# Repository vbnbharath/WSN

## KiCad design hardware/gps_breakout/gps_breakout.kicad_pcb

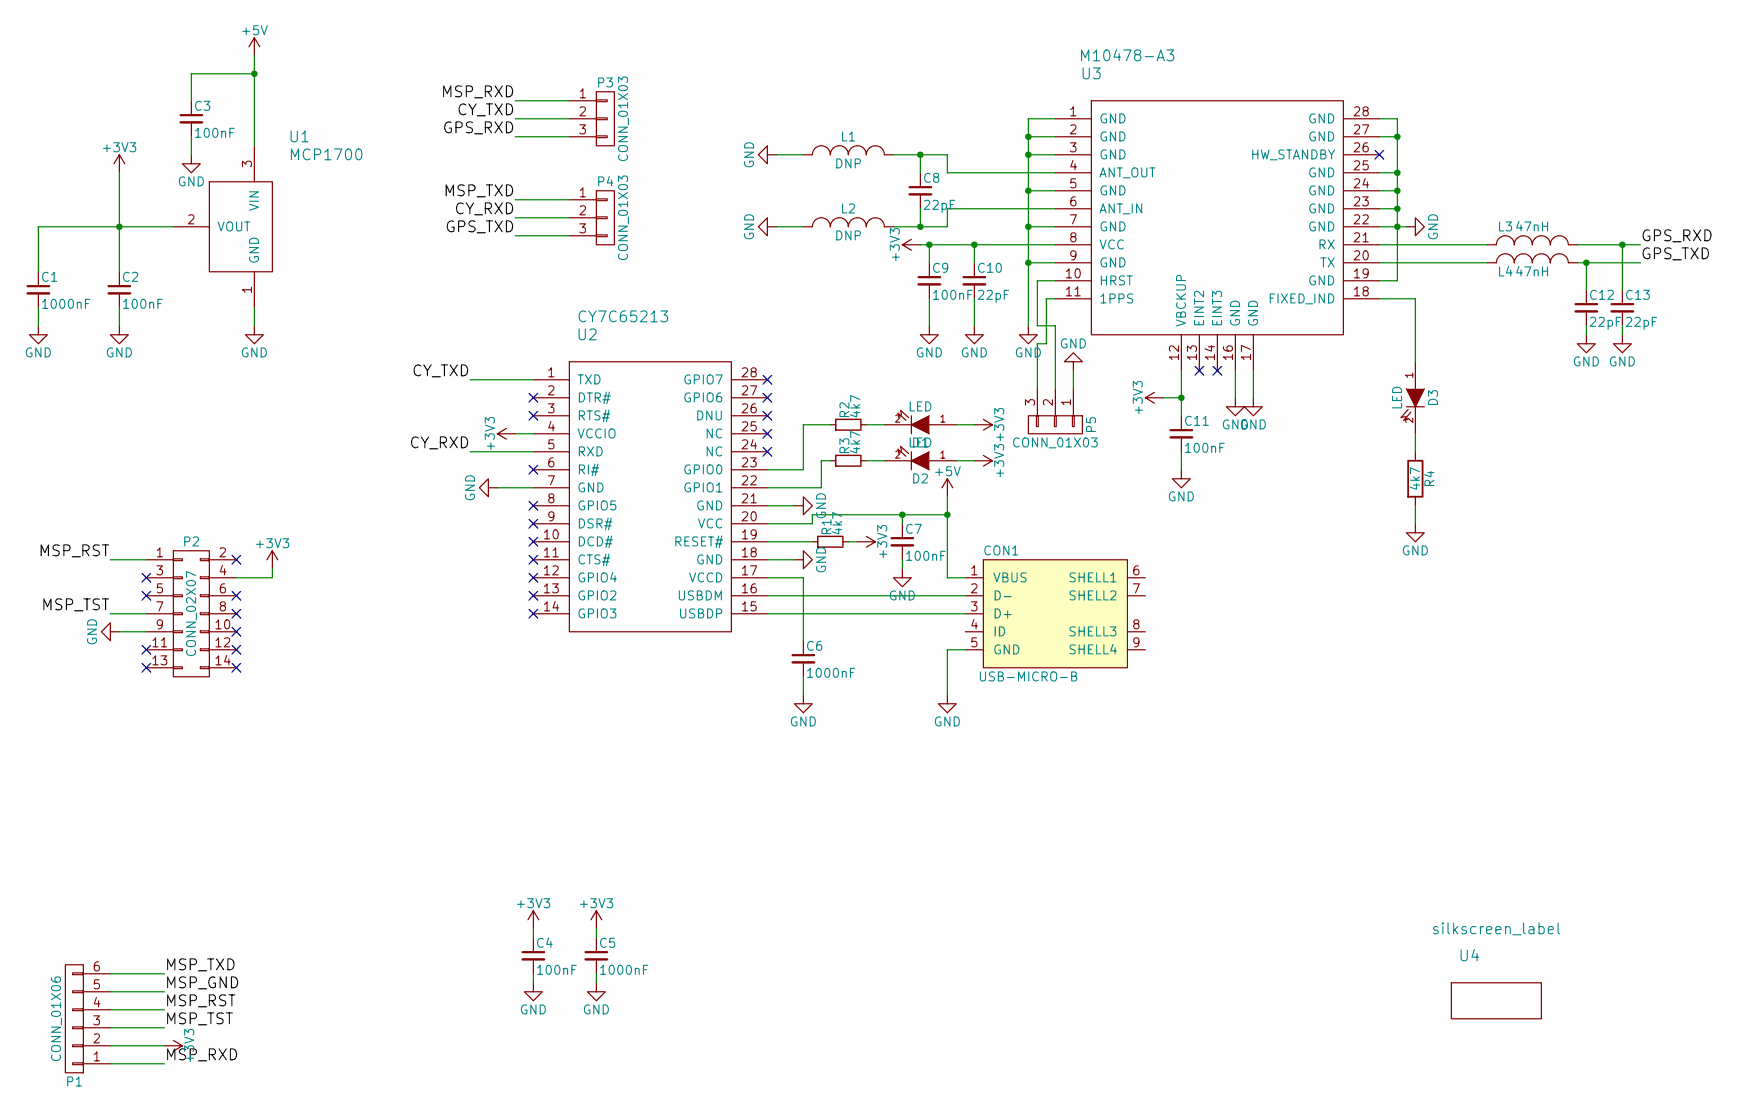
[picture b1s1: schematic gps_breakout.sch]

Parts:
C1, C5, C6: 1000nF; C_0603
C2, C3, C4, C7, C9, C11: 100nF; C_0603
C8, C10, C12, C13: 22pF; C_0603
CON1: USB-MICRO-B; USB_Mini-B
D1, D2, D3: LED; LED-0603
L1, L2: DNP; R_0603
L3, L4: 47nH; R_0603
P1: CONN_01X06; LPPB061NGCN-RC
P2: CONN_02X07; CONN_MSPJTAG
P3, P4, P5: CONN_01X03; JMP_HDR
R1, R2, R3, R4: 4k7; R_0603
U1: MCP1700; SOT89-3_Housing
U2: CY7C65213; SSOP-28_5.3x10.2mm_Pitch0.65mm
U3: M10478-A3; gps_radionova
U4: silkscreen_label; gunter

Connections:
+3V3: C1.1, C2.1, C4.1, C5.1, C9.1, C10.1, C11.1, D1.1 (A), D2.1 (A), P1.2, P2.4, R1.2, U1.2 (VOUT), U2.4 (VCCIO), U3.8 (VCC), U3.12 (VBCKUP)
+5V: C3.1, C7.1, CON1.1 (VBUS), U1.3 (VIN), U2.20 (VCC)
/CY_RXD: P4.2, U2.5 (RXD)
/CY_TXD: P3.2, U2.1 (TXD)
/GPS_RXD: C13.1, L3.2, P3.3
/GPS_TXD: C12.1, L4.2, P4.3
/MSP_GND: P1.5
/MSP_RST: P1.4, P2.1
/MSP_RXD: P1.1, P3.1
/MSP_TST: P1.3, P2.7
/MSP_TXD: P1.6, P4.1
GND: C1.2, C2.2, C3.2, C4.2, C5.2, C6.2, C7.2, C9.2, C10.2, C11.2, C12.2, C13.2, CON1.5 (GND), L1.1, L2.1, P2.9, P5.1, R4.2, U1.1 (GND), U2.7 (GND), U2.18 (GND), U2.21 (GND), U3.1 (GND), U3.2 (GND), U3.3 (GND), U3.5 (GND), U3.7 (GND), U3.9 (GND), U3.16 (GND), U3.17 (GND), U3.19 (GND), U3.22 (GND), U3.23 (GND), U3.24 (GND), U3.25 (GND), U3.27 (GND), U3.28 (GND)
unnamed: C6.1, U2.17 (VCCD)
unnamed: C8.1, L1.2, U3.4 (ANT_OUT)
unnamed: C8.2, L2.2, U3.6 (ANT_IN)
unnamed: CON1.2 (D-), U2.16 (USBDM)
unnamed: CON1.3 (D+), U2.15 (USBDP)
unnamed: D1.2 (K), R2.2
unnamed: D2.2 (K), R3.2
unnamed: D3.1 (A), U3.18 (FIXED_IND)
unnamed: D3.2 (K), R4.1
unnamed: L3.1, U3.21 (RX)
unnamed: L4.1, U3.20 (TX)
unnamed: P5.2, U3.10 (HRST)
unnamed: P5.3, U3.11 (1PPS)
unnamed: R1.1, U2.19 (RESET#)
unnamed: R2.1, U2.23 (GPIO0)
unnamed: R3.1, U2.22 (GPIO1)

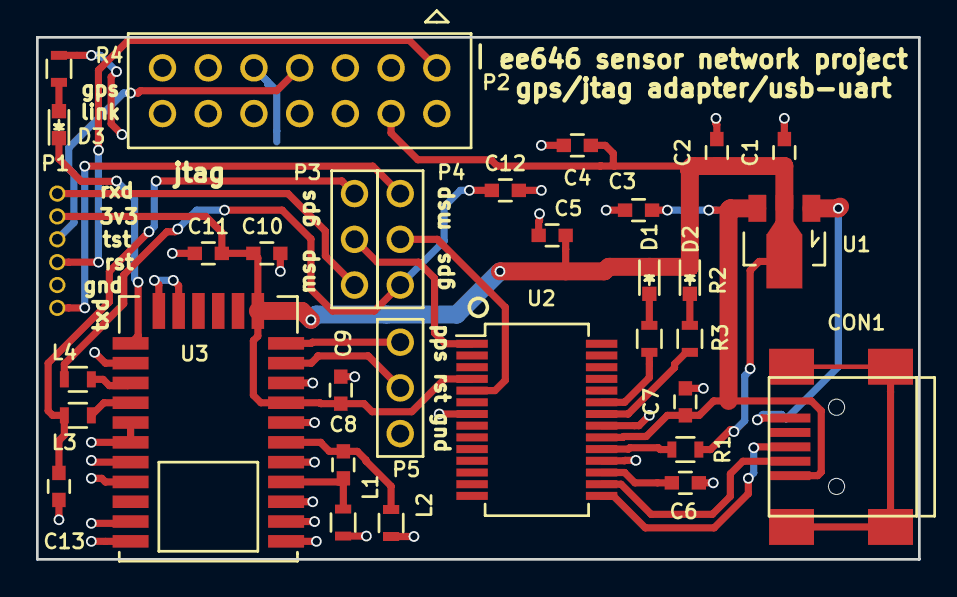
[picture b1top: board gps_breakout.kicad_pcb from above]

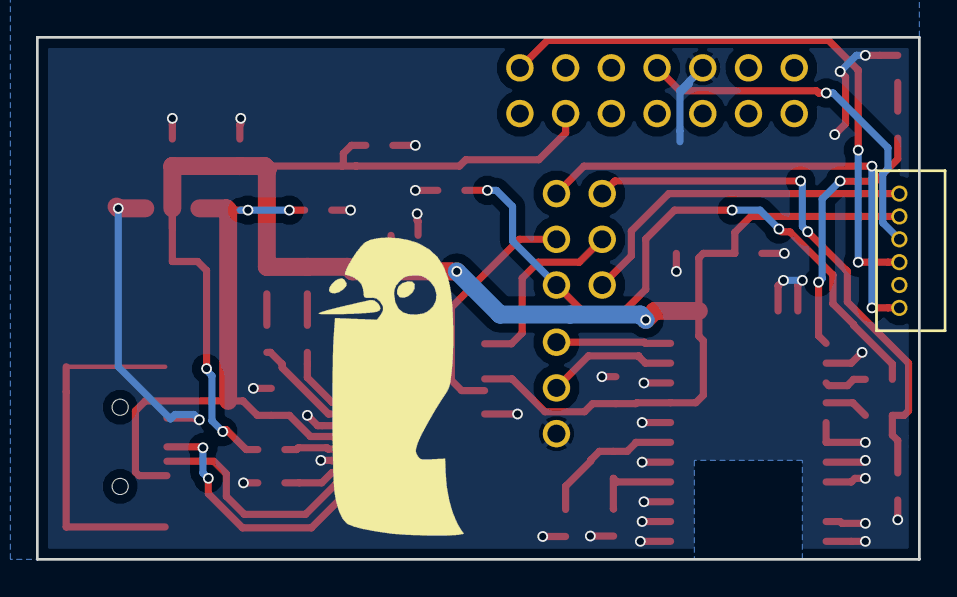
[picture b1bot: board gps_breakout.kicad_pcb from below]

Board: 2 copper layers, 49.0 x 29.0 mm, 34 parts (2 on the bottom side), 27 nets.

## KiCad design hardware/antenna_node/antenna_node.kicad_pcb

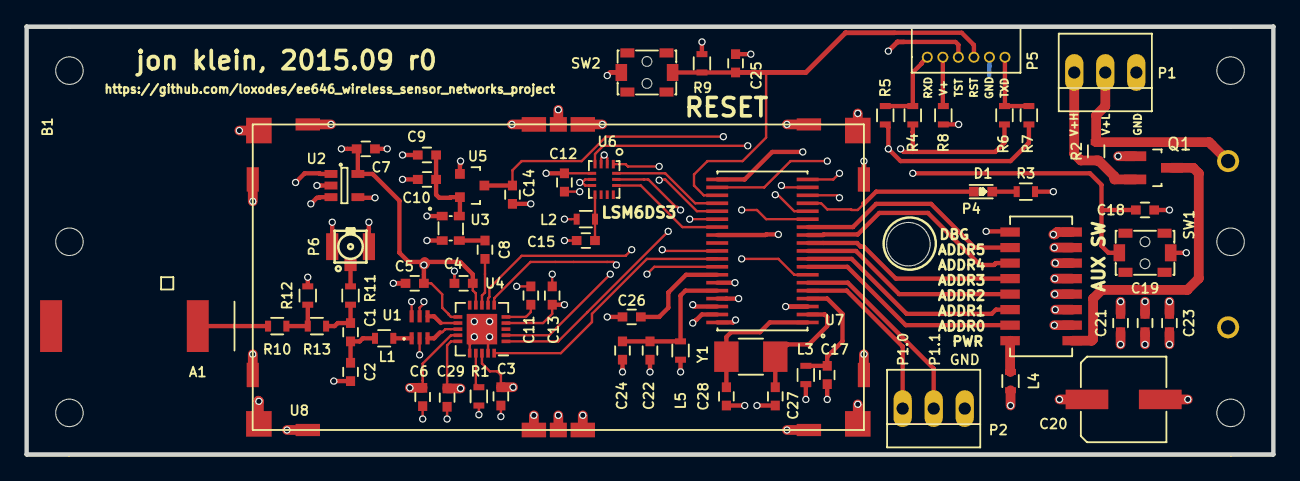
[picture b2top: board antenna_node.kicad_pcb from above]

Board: 4 copper layers, 102.0 x 35.0 mm, 67 parts (1 on the bottom side), 58 nets.

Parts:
A1: Antenna_2port; ANT1204LL05R0915A
B1: 1555C2F22GY; 1555CF22
C1, C23: 100 pF NPO; C_0603
C2: 1.8 pF; C_0603
C3, C4, C5, C6, C7, C8, C9, C11, C12, C13, C14, C15, C17, C19, C24, C29: 100 nF; C_0603
C10, C22: 1000 nF; C_0603
C18, C21, C25: 1 nF; C_0603
C20: 220 uF; CAP_POL_6p60mm
C26: 470 nF; C_0603
C27, C28: 10 pF; C_0603
D1: RED; LED-0603
L1: 5.6 nH; R_0603
L2, L3, L4, L5: 2.2 kOhm; R_0603
P1, P2: CONN_01X03; PINHEAD1-3
P3: CONN_01X02; BC2AAPC
P4: DIL16; CHS-08TA
P5: CONN_01X06; LPPB061NGCN-RC
P6: CONN_01X03; U.FL-COAX
Q1: Q_PMOS_GDS; SOT-23_Handsoldering
R1, R3, R9: 56k; R_0603
R2: 1; R_0603
R4, R5, R6, R7, R10, R13: 0; R_0603
R8, R11, R12: DNP; R_0603
SW1, SW2: SW_PUSH; PTS820J20MSMTRLFS
U1: 0896BM15A0001; 0896BM15A0001E
U2: TC77; SOT-23-5
U3: TCXO; NT2016SA
U4: CC110L; QFN-20-1EP_4x4mm_Pitch0.5mm
U5: MCP1700; SOT-23
U6: LSM6DS3; ST_LGA_14
U7: MSP430FR5739; TSSOP_38_Pitch0.65mm
U8: S01-50250500
Y1: Crystal_Small; R_1210_HandSoldering

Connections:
/AUXLED0: D1.1, U7.16
/AUXSW0: C18.1, SW1.1, U7.17
/CC_CSn: U4.7, U7.29
/CC_GDO: U4.6, U7.7
/CC_SCLK: U4.1, U7.25
/CC_SI: U4.20, U7.30
/CC_SO: U4.2, U7.31
/LSM_CS: U6.12, U7.26
/LSM_INT1: U6.4, U7.18
/LSM_MISO: U6.1, U7.24
/LSM_MOSI: U6.14, U7.23
/LSM_SCLK: U6.13, U7.14
/MCU_RXD: R4.2, R6.2, U7.20
/MCU_TXD: R5.2, R7.2, U7.19
/MSP_VCORE: C26.1, U7.32
/RST: C25.1, P5.4, R9.2, SW2.1, U7.22
/SWADDR0: P4.7, U7.8
/SWADDR1: P4.6, U7.9
/SWADDR2: P4.5, U7.10
/SWADDR3: P4.4, U7.11
/SWADDR4: P4.3, U7.12
/SWADDR5: P4.2, U7.13
/SWDEBUG: P4.1, U7.27
/TC_CS: U2.1, U7.36
/TC_SCK: U2.3, U7.35
/TC_SIO: U2.4, U7.37
/TST: P5.3, U7.21
/XTAL_EN: C14.1, U5.3, U7.15
GND: C2.2, C3.2, C4.2, C5.2, C6.2, C7.2, C9.2, C10.2, C11.2, C12.2, C13.2, C14.2, C15.2, C17.2, C18.2, C19.2, C20.2, C21.2, C22.2, C23.2, C24.2, C25.2, C26.2, C27.1, C28.1, C29.2, P1.1, P2.1, P3.2, P4.10, P4.11, P4.12, P4.13, P4.14, P4.15, P4.16, P5.5, P6.2, P6.3, Q1.1, R1.1, R3.2, R12.1, SW1.2, SW2.2, U1.2, U1.5, U1.6, U2.2, U3.1, U3.2, U4.16, U4.19, U4.21, U5.1, U6.2, U6.3, U6.6, U6.7, U7.3, U7.33, U7.38, U8.1, U8.2, U8.3, U8.4, U8.5, U8.6, U8.7, U8.8, U8.9, U8.10, U8.11, U8.12, U8.13, U8.14, U8.15, U8.16, U8.17, U8.18
unnamed: A1.1, R10.2
unnamed: C1.1, C2.1, L1.1
unnamed: C1.2, R11.1, R13.1
unnamed: C8.1, U4.8
unnamed: C8.2, U3.3
unnamed: C9.1, C10.1, U3.4, U5.2
unnamed: C11.1, U4.5
unnamed: C15.1, L2.1, U6.8
unnamed: C17.1, L3.1, U7.4
unnamed: C22.1, C24.1, L5.1, U7.34
unnamed: C27.2, U7.2, Y1.1
unnamed: C28.2, U7.1, Y1.2
unnamed: D1.2, R3.1
unnamed: L1.2, U1.1
unnamed: L4.1, P4.8
unnamed: P1.2, P3.1, R2.2
unnamed: P1.3, Q1.2, R2.1
unnamed: P2.2, U7.6
unnamed: P2.3, U7.5
unnamed: P4.9, Q1.3
unnamed: P5.1, R4.1, R5.1
unnamed: P5.2, R8.1
unnamed: P5.6, R6.1, R7.1
unnamed: P6.1, R11.2
unnamed: R1.2, U4.17
unnamed: R10.1, R12.2, R13.2
unnamed: U1.3, U4.13
unnamed: U1.4, U4.12
VCC: C3.1, C4.1, C5.1, C6.1, C7.1, C12.1, C13.1, C19.1, C20.1, C21.1, C23.1, C29.1, L2.2, L3.2, L4.2, L5.2, R8.2, R9.1, U2.5, U4.4, U4.9, U4.11, U4.14, U4.15, U4.18, U6.5

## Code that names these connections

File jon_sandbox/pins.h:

#define LEDOUT PJOUT
#define LEDDIR PJDIR
#define LED1 BIT1

// uart pins
#define UARTOUT P2OUT
#define UARTSEL P2SEL0
#define UARTDIR P2DIR
#define RXD (1 << 6)
#define TXD (1 << 5)

// switches and LEDs
#define SWADDR0_PIN (1 << 0)
#define SWADDR0_OUT P3OUT
#define SWADDR0_DIR P3DIR

#define SWADDR1_PIN (1 << 1)
#define SWADDR1_OUT P3OUT
#define SWADDR1_DIR P3DIR

#define SWADDR2_PIN (1 << 2)
#define SWADDR2_OUT P3OUT
#define SWADDR2_DIR P3DIR

#define SWADDR3_PIN (1 << 3)
#define SWADDR3_OUT P3OUT
#define SWADDR3_DIR P3DIR

#define SWADDR4_PIN (1 << 3)
#define SWADDR4_OUT P1OUT
#define SWADDR4_DIR P1DIR

#define SWADDR5_PIN (1 << 4)
#define SWADDR5_OUT P1OUT
#define SWADDR5_DIR P1DIR

#define SWDEBUG_PIN (1 << 5)
#define SWDEBUG_OUT P3OUT
#define SWDEBUG_DIR P3DIR
#define SWDEBUG_REN P3REN
#define SWDEBUG_IN P3IN

#define SWAUX0_PIN (1 << 2)
#define SWAUX0_OUT PJOUT
#define SWAUX0_DIR PJDIR
#define SWAUX0_REN PJREN
#define SWAUX0_IN PJIN

#define LED0_PIN (1 << 1)
#define LED0_OUT PJOUT
#define LED0_DIR PJDIR


// cc110L pins, SPI on UB0
#define CC_SCK_PIN (1 << 2)
#define CC_SCK_OUT P2OUT
#define CC_SCK_DIR P2DIR
#define CC_SCK_SEL P2SEL0

#define CC_MISO_PIN (1 << 7)
#define CC_MISO_OUT P1OUT
#define CC_MISO_DIR P1DIR
#define CC_MISO_SEL P1SEL0

#define CC_MOSI_PIN (1 << 6)
#define CC_MOSI_OUT P1OUT
#define CC_MOSI_DIR P1DIR
#define CC_MOSI_SEL P1SEL0

#define CC_CG0_OUT P1OUT
#define CC_CG0_PIN (1 << 2)
#define CC_CG0_DIR P1DIR

#define CC_CS_OUT P3OUT
#define CC_CS_DIR P3DIR
#define CC_CS_PIN (1 << 7)

#define CC_XTAL_OUT PJOUT
#define CC_XTAL_DIR PJDIR
#define CC_XTAL_PIN (1 << 0)

// tc77 pins, SPI is bitbanged
#define TC_OUT P2OUT
#define TC_DIR P2DIR
#define TC_SIO_PIN (1 << 4)
#define TC_CS_PIN (1 << 3)
#define TC_SCK_PIN (1 << 7)

// lsm6ds3 pins, SPI on UA0
#define LSM_INT1_OUT PJOUT
#define LSM_INT1_DIR PJDIR
#define LSM_INT1_SEL PJSEL0
#define LSM_INT1_PIN (1 << 3)

#define LSM_MISO 
#define LSM_MOSI_OUT P2OUT
#define LSM_MOSI_DIR P2DIR
#define LSM_MOSI_SEL P2SEL0
#define LSM_MOSI_PIN (1 << 0)

#define LSM_MISO_OUT P2OUT
#define LSM_MISO_DIR P2DIR
#define LSM_MISO_SEL P2SEL0
#define LSM_MISO_PIN (1 << 1)

#define LSM_CS_OUT P3OUT
#define LSM_CS_DIR P3DIR
#define LSM_CS_SEL P3SEL0
#define LSM_CS_PIN (1 << 4)

#define LSM_SCK_OUT P1OUT
#define LSM_SCK_DIR P1DIR
#define LSM_SCK_SEL P1SEL0
#define LSM_SCK_PIN (1 << 5)

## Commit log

2015-10-13 Initial Push
2015-10-13 no message
2015-10-14 Added pindefs file and ifdefs to Stikine for platform compatibility.
2015-10-14 added (non-functional) code to use radios on sensor node hardware
2015-10-14 added kicad files for sensor node hardware
2015-10-15 Complete COM port communication for heartbeat ticker.
2015-10-16 Changed to stdint numeric types. Added working SPI library to Stikine
2015-10-16 Fixed spinlock for CC110l wakeup on SPI
2015-10-16 Removed return value from Wait_For_CCWake()
2015-10-17 Added burst Send/Read to SPI library Adapted CC1100 Header file for CC110l and added it to project.
2015-10-17 Fixed an issue where the RX complete flag would not be cleared in the SPI_Read function. This could cause issues with read commands issued after a send or in rapid succession.
2015-10-18 Added Strobe command to SPI library Got basic radio hello world program working, push button on one board to light up LED on another.
2015-10-19 blinking lights of radio works! (fixed bug in SPI..)
2015-10-20 Broke SPI pin defines into a separate library.
2015-10-21 Changed pin settings to accommodate the external 32768 crystal.
2015-10-21 Added Status register read to SPI Library.
2015-10-21 Finished documenting the SPI library and included the doxygen output.
2015-10-22 added gps breakout schematic
2015-10-23 started layout of gps board
2015-10-24 started merging in code for msp430fr5739 support
2015-10-24 finished layout of gps board
2015-10-24 ordered gps board
2015-10-25 added BOM, ordered components
2015-10-26 removed temp file
2015-10-26 switch to quotes for local header files for GCC compatibility
2015-10-26 (untested) changes for msp430fr5739 support
2015-10-27 started on fine grained localization with GPS
2015-10-27 wrote (untested) GPS driver, started on localization
2015-10-27 LBT Possibly working
2015-10-29 more incomplete and untested code for gps localization.. waiting on hardware
2015-10-30 work during class, added kml exporting of sensor map
2015-10-30 Got receiver working on one channel. Soon to be sniffing.
    Best code ever.
2015-11-03 added some notes on localization model
2015-11-04 added a few scraps of localization work.. still need to write propagation model..
2015-11-10 Testing the Sniffer, made minor changes
2015-11-10 Code for spamming a channel.
2015-11-10 Nothing Really Changed, Just more testing with comments and whatnot
2015-11-10 a bit more work on localization.
2015-11-13 fixed p(rssi) lookup table generation
2015-11-13 More comments and testing.
2015-11-13 Sniffer Testing with changing addresses
2015-11-13 Working Packet Filter.
2015-11-17 localization with known shadowing/path loss appears to work
2015-11-18 Timer code version 1
2015-11-18 Some progress
2015-11-19 Added a line to enable global interrupts in the init function.
    SPI library now appears to be working.
2015-11-19 improved visualization of localization
2015-11-19 Much Progress, UART, Listen on Channel at Will, Much Wow
2015-11-20 added schematic pdf for sensor node
2015-11-21 Fixed issue where LBT_Send would get stuck in LPM3.
2015-11-21 Sleep_timer works fine.
2015-11-21 Added state machine enum to main.
2015-11-21 Some small name tweaks, changed variables to use stdint types.
2015-11-21 Most recent code for the sniffer, should have the output format correctly for RSSI display and data. Supposed to do new line as well but was not on tuesday for whatever reason.
2015-11-21 Changed LBT Library to use Sleep_Timer instead of delay cycles. Added global break variable to use with sleep library. Changed LBT_Listen to return a struct.
2015-11-21 Tweaked main loop.
2015-11-22 added rssi logging script, untested incomplete gps localization processing
2015-11-22 added rssi logs from walking around taku
2015-11-23 Small tweaks to LBT library.
2015-11-24 Updates to the DoxyFile. Renamed the LBT libraries to just 'Radio'
2015-11-24 Adjusted the call to Convert_to_hex to include the last byte in the payload. Some small formatting changes.
2015-11-24 Skeleton code ready for addition of clustering code.
2015-11-24 Documentation updates
2015-11-24 Testing Sniffer
2015-11-24 Changed Main Loop
2015-11-24 Most Recent Sniffer
2015-11-24 Fixed the main loop
2015-11-24 Fixed timer init.
2015-11-24 Fixed an issue where an interrupt with no handler was being called.
2015-11-25 Added base temperature measurement using automatic data transfer.
2015-11-25 Fixed an issue with sleep timer, TA0CCR1 was accidentally used in place of TA0CCTL1
2015-11-25 Fixed an issue with the sleep timer, where TA0CCR1 was accidentally used where TA0CCTL1 should have been
2015-11-29 Got temperature measurements working.
2015-11-29 Removed unnecessary volatile qualifiers from variables.
2015-11-29 Added a send function to the radio library for use in TDMA mode (does not perform CSMA).
2015-11-29 Added two functions: one divides uint16_t into two uint8_t, another merges two uint8_t into uint16_t for sending messages over radio.
2015-11-30 Working on TDMA
2015-11-30 int_divide works
2015-11-30 CH part that sends TDMA schedule works
2015-11-30 Continue working on TDMA
